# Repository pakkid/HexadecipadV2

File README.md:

# HexadecipadV2

A fully customizable macro pad with 24 mechanical switches and 4 rotary encoders, designed with KiCAD and featuring an little baby RP2040 microcontroller.

## Overview

HexadecipadV2 is hackpad designed for the blueprint/hackpad ysws. I spent about 6 hours pulling my hair out over case design before I knew what I was doing... ps. I still have no idea what I'm doing.

**Key Features:**
- 24 hot-swap MX-compatible mechanical switches (oops)
- 4 rotary encoders for volume control, scrolling, or custom functions (more oops)
- Seeed Studio XIAO RP2040 microcontroller
- MCP23017 I/O expander because XIAO RP2040 is little baby.
- Open-source KiCAD design because i broke.
- 3D-printed case 👍
- Too many inputs. checked with Blueprint Support, they said its fine as long as I pay.
- Too big pcb (100mmx130mm) also checked with Blueprint staff.
- Fully custom vibe coded garbage script that send serial to a python script on my pc so we can modify keys without having to use stupid kmk.

## Project Structure (just the READMEs for when you access on github.io)

```
HexadecipadV2/
├── CAD/                     # Case and mechanical design files
│   └── README.md            # CAD file documentation
├── Firmware/                # Source firmware code
│   └── README.md            # Firmware documentation
├── PCB/                     # KiCad PCB design files
│   └── HexadecipadV2/       # Main PCB project
│       └── README.md        # PCB documentation
├── Production/              # Manufacturing-ready files
│   ├── CAD/                 # STL files for 3D printing
│   │   └── README.md        # 3D printing guide
│   ├── Firmware/            # Production firmware
│   │   └── README.md        # Firmware installation guide
│   ├── PCB/                 # Gerber files for PCB fab
│   │   └── README.md        # PCB ordering guide
│   └── README.md            # Production overview
└── Other files/             # Supporting files
    ├── 3d models/           # Component STEP models
    │   └── README.md        # 3D models documentation
    ├── images/              # Documentation images
    │   └── README.md        # Images documentation
    └── README.md            # Other files overview
```

### Links and stuff
- **[CAD Files](CAD/)** - Case design and mechanical files
- **[Firmware](Firmware/)** - Source code and development files
- **[PCB Design](PCB/)** - KiCad project and design files
- **[Production Files](Production/)** - Ready-to-manufacture files
  - [3D Printable Case Files](Production/CAD/)
  - [Production Firmware](Production/Firmware/)
  - [PCB Manufacturing Files](Production/PCB/)
- **[Other Files](Other%20files/)** - Component models and documentation images
 
## Screenshots

### Hackpad

### Schematic

### PCB

**PCB Filled:**

**PCB Unfilled:**

### Case Assembly

## Bill of Materials (BOM)

| # | References | Value | Footprint | Quantity |
|---|------------|-------|-----------|----------|
| 1 | R1, R2 | R | R_Axial_DIN0207_L6.3mm_D2.5mm_P7.62mm_Horizontal | 2 |
| 2 | D1–D28 | D | D_DO-35_SOD27_P7.62mm_Horizontal | 28 |
| 3 | U1 | XIAO-RP2040-DIP | XIAO-RP2040-DIP | 1 |
| 4 | U2 | MCP23017_SP | DIP-28_W7.62mm | 1 |
| 5 | SW5–SW28 | SW_Push_45deg | MX-Hotswap-1U | 24 |
| 6 | SW1–SW4 | Encoder | RotaryEncoder_Alps_EC11E-Switch_Vertical_H20mm | 4 |
| 7 | N/A | M3x16mm screws | N/A | 4 |

 - **[Interactive BOM](https://hxdcpd.stuffandthings.cc/PCB/HexadecipadV2/bom/ibom.html)**

## Design Files

- **Schematic:** [PCB/HexadecipadV2/HexadecipadV2.kicad_sch](PCB/HexadecipadV2/HexadecipadV2.kicad_sch)
- **PCB Layout:** [PCB/HexadecipadV2/HexadecipadV2.kicad_pcb](PCB/HexadecipadV2/HexadecipadV2.kicad_pcb)
- **PCB 3D Model:** [PCB/HexadecipadV2/HexadecipadV2.step](PCB/HexadecipadV2/HexadecipadV2.step)
- **Case Design:** [CAD/HexadecipadV2-assembled.step](CAD/HexadecipadV2-assembled.step)

### Firmware

Have a look at [Firmware](Firmware/) to see my stupid code.

## License

This project is licensed under the MIT License - see the [LICENSE](LICENSE) file for details.

## Contributing

Contributing will probably end up with me being fried because of my terrible everything in this project.

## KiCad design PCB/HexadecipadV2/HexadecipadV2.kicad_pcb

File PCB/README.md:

# PCB Directory

This directory contains the printed circuit board (PCB) design files for HexadecipadV2.

## Subdirectories

### HexadecipadV2/
Main PCB design directory containing all KiCad project files:

#### Project Files
- **HexadecipadV2.kicad_pro** - KiCad project file
- **HexadecipadV2.kicad_sch** - KiCad schematic file
- **HexadecipadV2.kicad_pcb** - KiCad PCB layout file
- **HexadecipadV2.kicad_prl** - KiCad project local settings
- **HexadecipadV2.step** - 3D model export of the PCB

#### Configuration Files
- **fp-lib-table** - Footprint library table
- **sym-lib-table** - Symbol library table
- **fp-info-cache** - Footprint information cache

#### Subdirectories
- **3d models/** - Component 3D models for PCB visualization
- **bom/** - Bill of Materials files (includes `ibom.html` - Interactive HTML BOM)
- **libraries/** - Custom KiCad libraries including footprints and symbols
  - `Hackpad/` - Custom Hackpad symbols and footprints
  - `kicad-keyboard-parts.pretty-master/` - Keyboard-specific footprints
  - `MX_V2-main/` - MX switch footprint library
  - `OPL_Kicad_Library-master/` - Open Parts Library
  - `RotaryEncoder/` - Rotary encoder components
- **HexadecipadV2-backups/** - Automatic KiCad backup files

## Software Requirements

- KiCad 7.0 or later (recommended for full compatibility)

## Usage

1. Open `HexadecipadV2.kicad_pro` in KiCad to view and edit the design
2. Use `ibom.html` in the `bom/` folder for assembly reference
3. For manufacturing files, see the `/Production/PCB/` directory

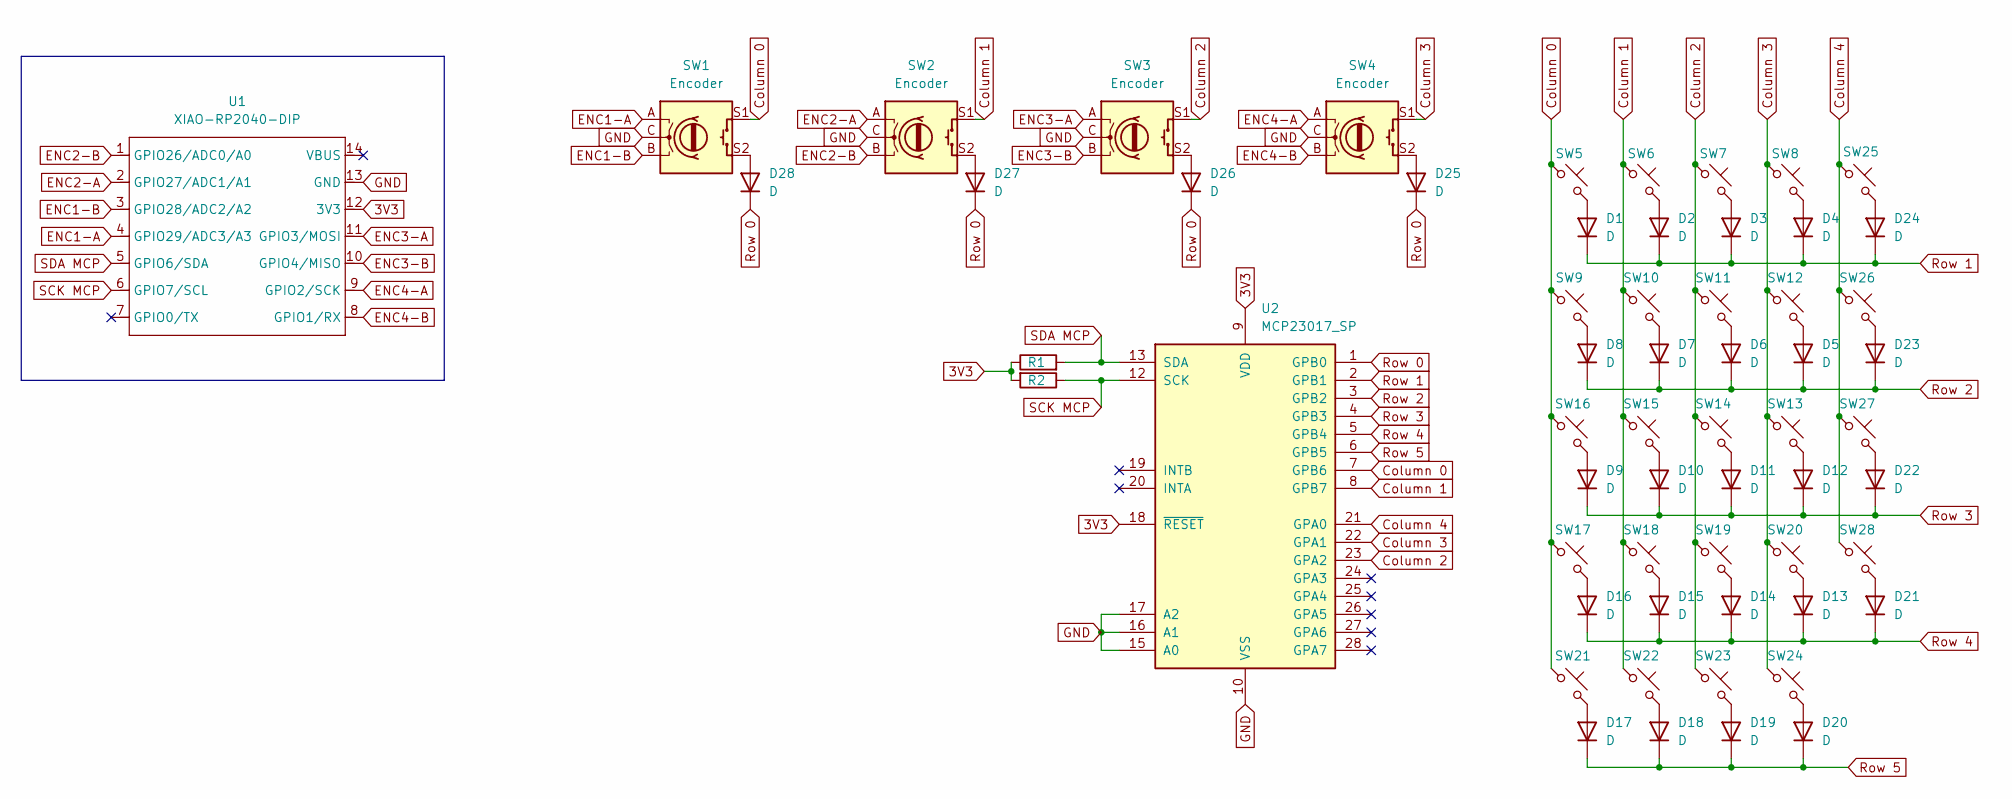
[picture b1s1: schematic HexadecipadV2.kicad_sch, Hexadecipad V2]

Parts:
D1, D2, D3, D4, D5, D6, D7, D8, D9, D10, D11, D12, D13, D14, D15, D16, D17, D18, D19, D20, D21, D22, D23, D24, D25, D26, D27, D28: D; D_DO-35_SOD27_P7.62mm_Horizontal
R1, R2: R; R_Axial_DIN0207_L6.3mm_D2.5mm_P7.62mm_Horizontal
SW1, SW2, SW3, SW4: Encoder; RotaryEncoder_Alps_EC11E-Switch_Vertical_H20mm
SW5, SW6, SW7, SW8, SW9, SW10, SW11, SW12, SW13, SW14, SW15, SW16, SW17, SW18, SW19, SW20, SW21, SW22, SW23, SW24, SW25, SW26, SW27, SW28: SW_Push_45deg; MX-Hotswap-1U
U1: XIAO-RP2040-DIP
U2: MCP23017_SP; DIP-28_W7.62mm

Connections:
3V3: R1.1, R2.2, U1.12 (3V3), U2.9 (VDD), U2.18 (~RESET)
Column 0: SW1.S1, SW5.1, SW9.1, SW16.1, SW17.1, SW21.1, U2.7 (GPB6)
Column 1: SW2.S1, SW6.1, SW10.1, SW15.1, SW18.1, SW22.1, U2.8 (GPB7)
Column 2: SW3.S1, SW7.1, SW11.1, SW14.1, SW19.1, SW23.1, U2.23 (GPA2)
Column 3: SW4.S1, SW8.1, SW12.1, SW13.1, SW20.1, SW24.1, U2.22 (GPA1)
Column 4: SW25.1, SW26.1, SW27.1, SW28.1, U2.21 (GPA0)
ENC1-A: SW1.A, U1.4 (GPIO29/ADC3/A3)
ENC1-B: SW1.B, U1.3 (GPIO28/ADC2/A2)
ENC2-A: SW2.A, U1.2 (GPIO27/ADC1/A1)
ENC2-B: SW2.B, U1.1 (GPIO26/ADC0/A0)
ENC3-A: SW3.A, U1.11 (GPIO3/MOSI)
ENC3-B: SW3.B, U1.10 (GPIO4/MISO)
ENC4-A: SW4.A, U1.9 (GPIO2/SCK)
ENC4-B: SW4.B, U1.8 (GPIO1/RX)
GND: SW1.C, SW2.C, SW3.C, SW4.C, U1.13 (GND), U2.10 (VSS), U2.15 (A0), U2.16 (A1), U2.17 (A2)
unnamed: D1.2 (A), SW5.2
unnamed: D2.2 (A), SW6.2
unnamed: D3.2 (A), SW7.2
unnamed: D4.2 (A), SW8.2
unnamed: D5.2 (A), SW12.2
unnamed: D6.2 (A), SW11.2
unnamed: D7.2 (A), SW10.2
unnamed: D8.2 (A), SW9.2
unnamed: D9.2 (A), SW16.2
unnamed: D10.2 (A), SW15.2
unnamed: D11.2 (A), SW14.2
unnamed: D12.2 (A), SW13.2
unnamed: D13.2 (A), SW20.2
unnamed: D14.2 (A), SW19.2
unnamed: D15.2 (A), SW18.2
unnamed: D16.2 (A), SW17.2
unnamed: D17.2 (A), SW21.2
unnamed: D18.2 (A), SW22.2
unnamed: D19.2 (A), SW23.2
unnamed: D20.2 (A), SW24.2
unnamed: D21.2 (A), SW28.2
unnamed: D22.2 (A), SW27.2
unnamed: D23.2 (A), SW26.2
unnamed: D24.2 (A), SW25.2
unnamed: D25.2 (A), SW4.S2
unnamed: D26.2 (A), SW3.S2
unnamed: D27.2 (A), SW2.S2
unnamed: D28.2 (A), SW1.S2
Row 0: D25.1 (K), D26.1 (K), D27.1 (K), D28.1 (K), U2.1 (GPB0)
Row 1: D1.1 (K), D2.1 (K), D3.1 (K), D4.1 (K), D24.1 (K), U2.2 (GPB1)
Row 2: D5.1 (K), D6.1 (K), D7.1 (K), D8.1 (K), D23.1 (K), U2.3 (GPB2)
Row 3: D9.1 (K), D10.1 (K), D11.1 (K), D12.1 (K), D22.1 (K), U2.4 (GPB3)
Row 4: D13.1 (K), D14.1 (K), D15.1 (K), D16.1 (K), D21.1 (K), U2.5 (GPB4)
Row 5: D17.1 (K), D18.1 (K), D19.1 (K), D20.1 (K), U2.6 (GPB5)
SCK MCP: R2.1, U1.6 (GPIO7/SCL), U2.12 (SCK)
SDA MCP: R1.2, U1.5 (GPIO6/SDA), U2.13 (SDA)

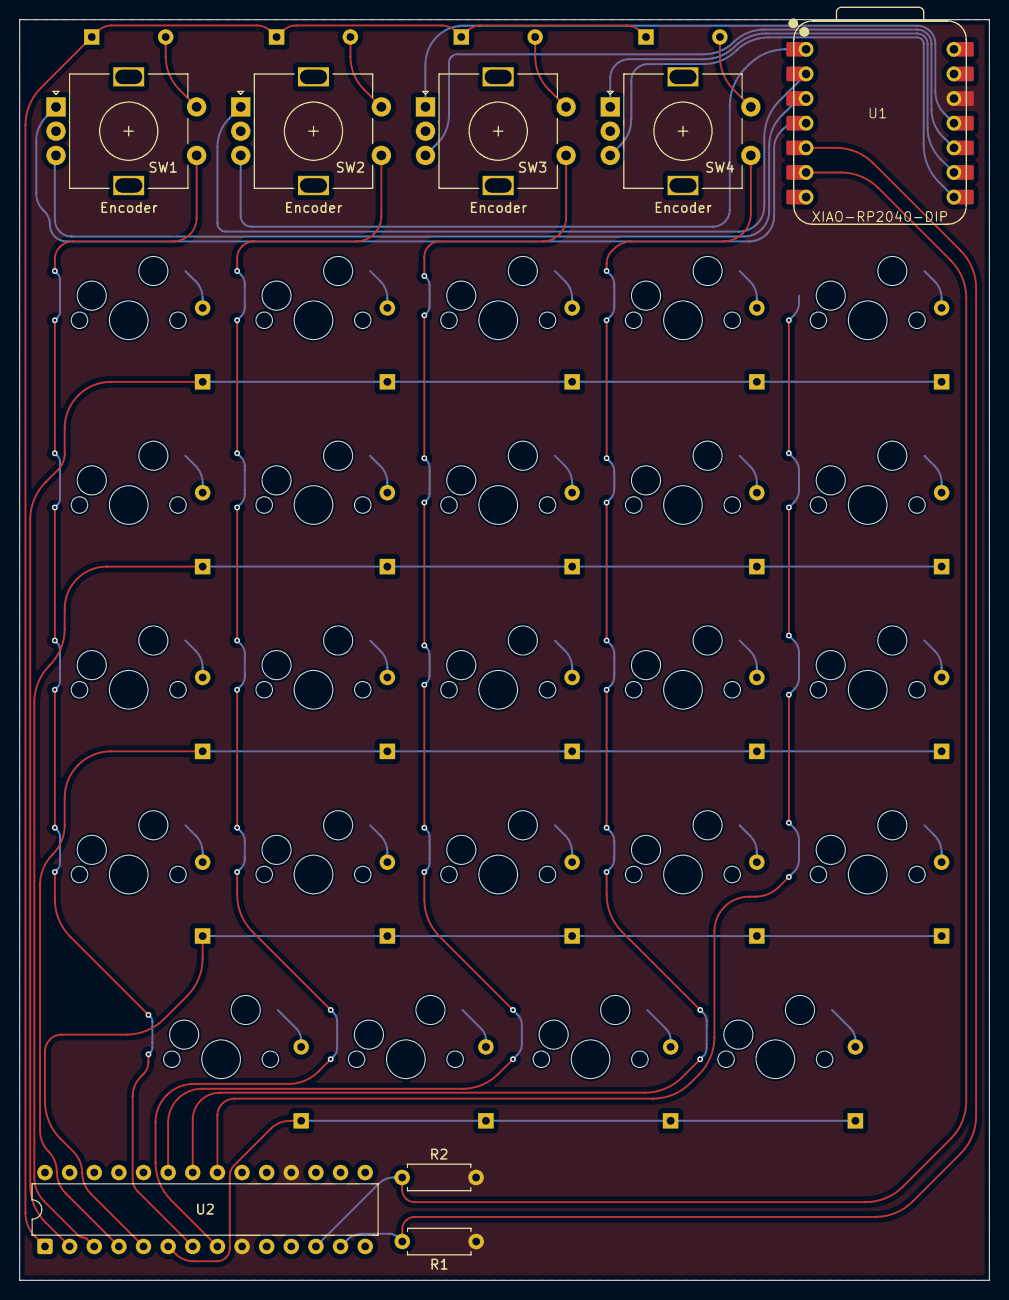
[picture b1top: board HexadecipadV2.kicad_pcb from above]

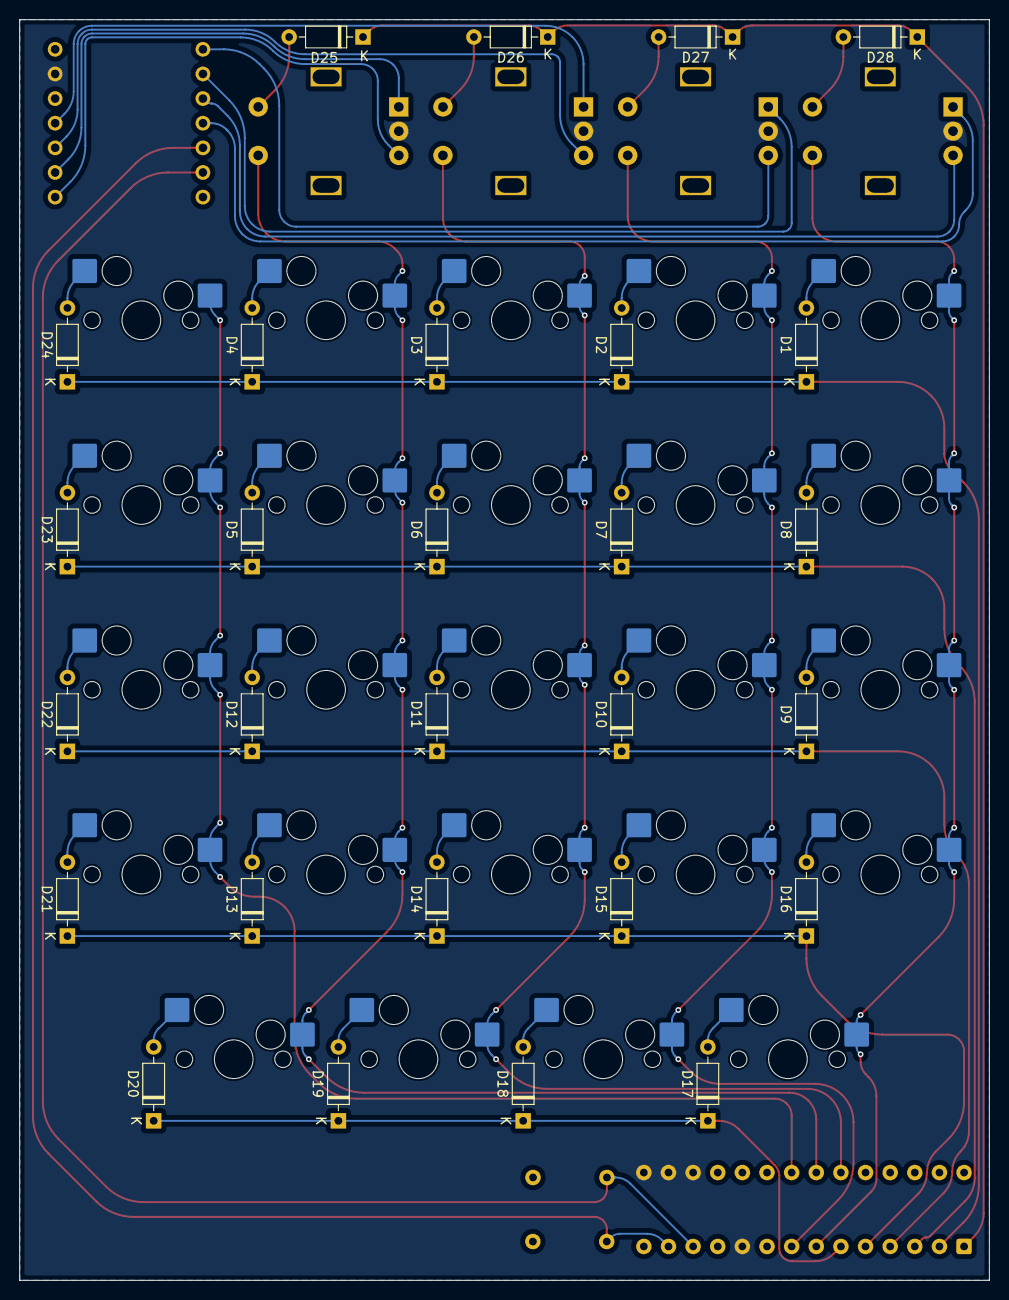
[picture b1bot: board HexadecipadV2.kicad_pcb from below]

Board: 2 copper layers, 100.0 x 130.0 mm, 60 parts (52 on the bottom side), 51 nets.

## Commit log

2026-01-02 Add everything
2026-01-05 Fix all traces
    I stopped using freerouting because i realised it was not allowed and it was a huge pain. redid all the traces by hand and made some power planes. removed all of my LEDs because 1.21 GIGAWATTS
2026-01-09 make the case
    took me 5 million years just to make this thing and it doesnt even look good
2026-01-23 added all my files after too long of not commiting
2026-01-23 Create CNAME
2026-01-23 Added screws
2026-01-26 Add Hexadecipad V2 control application and firmware files
2026-01-26 Add description of custom script for key modification in README.md
2026-01-26 add firmware and libraries to production folder
2026-01-27 Add production-ready files and documentation for CAD, firmware, and PCB
2026-01-27 Update README.md to enhance project structure and documentation links
2026-02-22 add screenshots of pcb prices
